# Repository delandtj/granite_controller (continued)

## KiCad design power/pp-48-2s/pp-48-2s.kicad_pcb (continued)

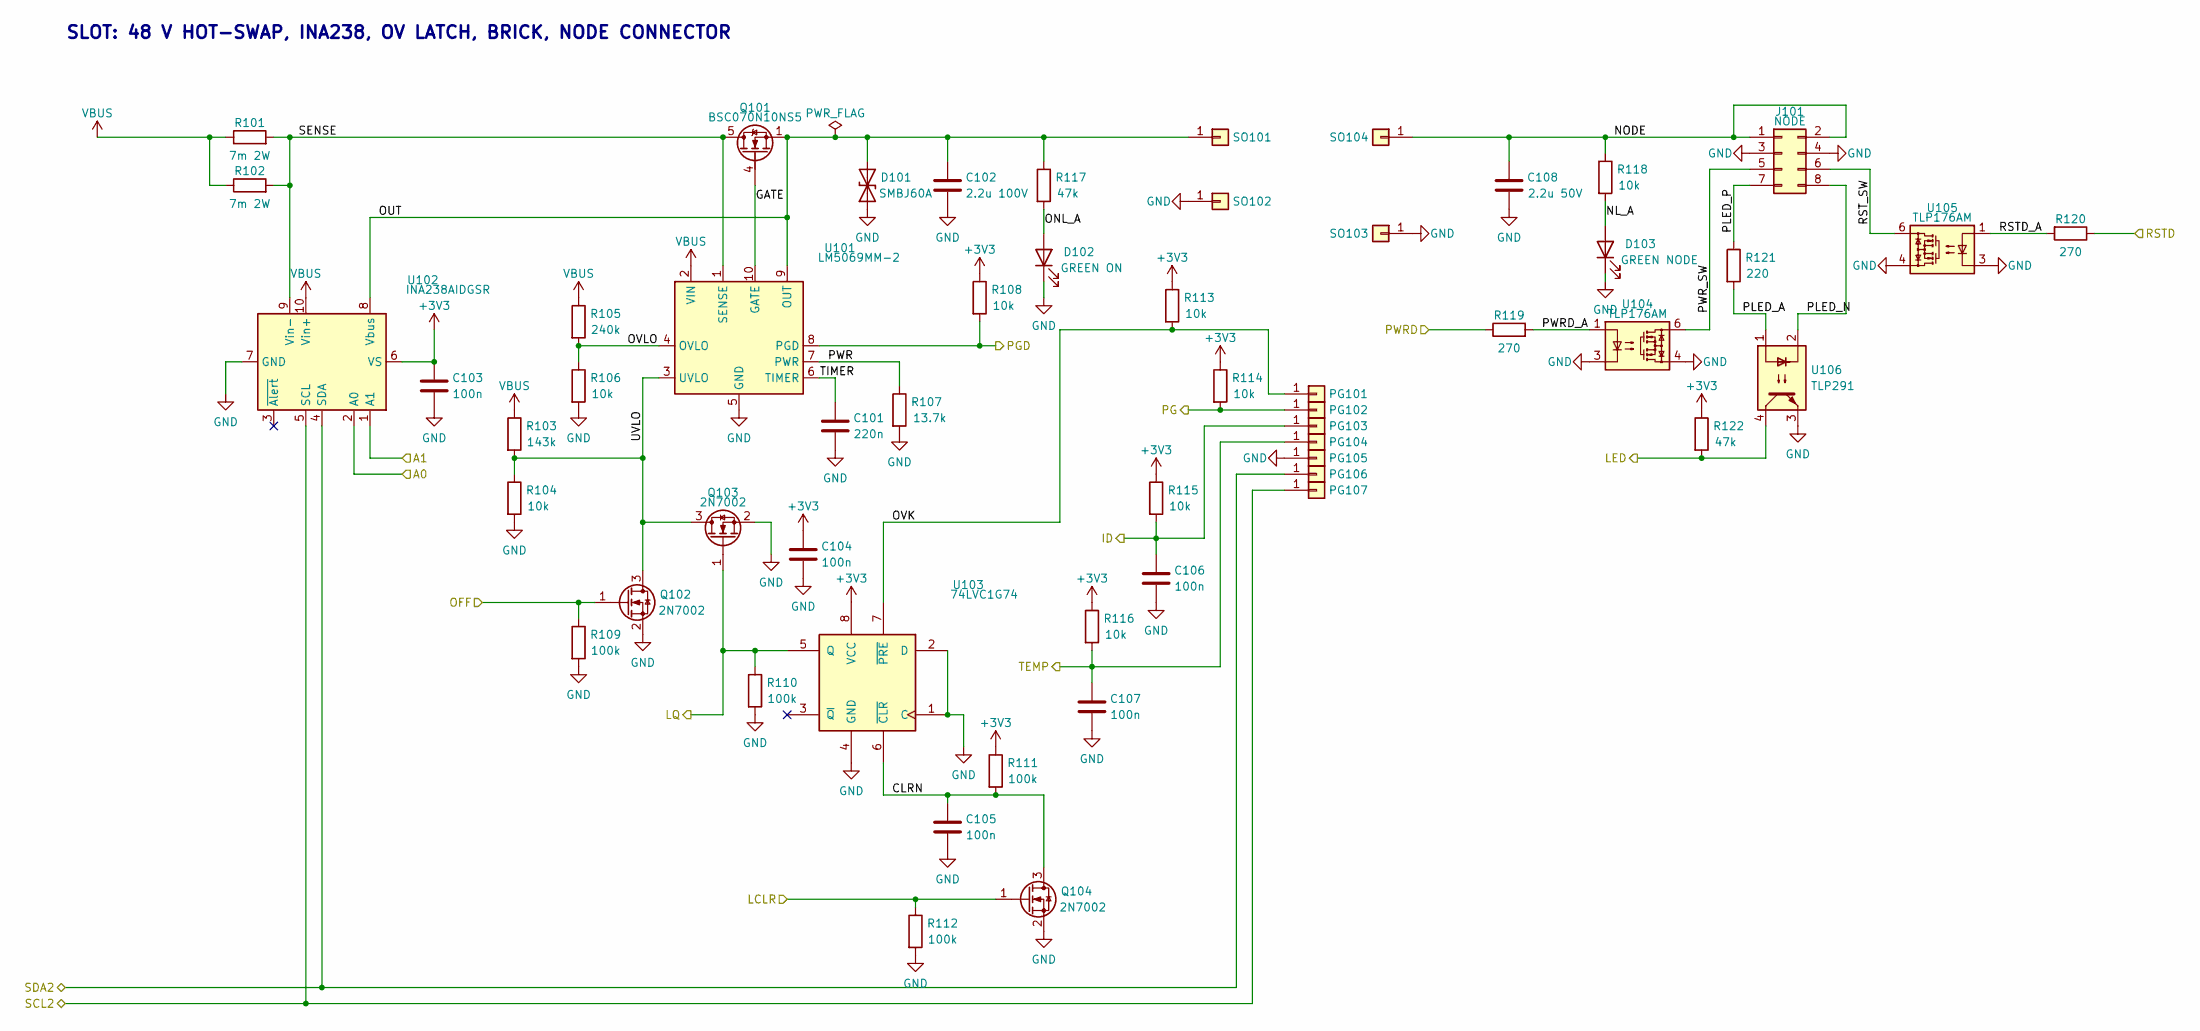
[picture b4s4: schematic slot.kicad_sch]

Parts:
C101: 220n; C_0603_1608Metric
C102: 2.2u 100V; C_1210_3225Metric; LCSC C338133
C103, C104, C105, C106, C107: 100n; C_0402_1005Metric; LCSC C1525
C108: 2.2u 50V; C_1210_3225Metric
D101: SMBJ60A; D_SMB; LCSC C353345
D102: GREEN ON; LED_0603_1608Metric; LCSC C2297
D103: GREEN NODE; LED_0603_1608Metric; LCSC C2297
J101: NODE; Molex_Mini-Fit_Jr_5566-08A_2x04_P4.20mm_Vertical; MPN Molex 39-28-1083
PG101, PG102, PG103, PG104, PG105, PG106, PG107: pogo; PM_Pogo_YZ130115073P; LCSC C5157258
Q101: BSC070N10NS5; TDSON-8-1
Q102, Q103, Q104: 2N7002; SOT-23; LCSC C8545
R101, R102: 7m 2W; R_2512_6332Metric; LCSC C2904232
R103: 143k; R_0805_2012Metric
R104, R106, R108, R113, R114, R115, R116: 10k; R_0402_1005Metric; LCSC C25744
R105: 240k; R_0805_2012Metric
R107: 13.7k; R_0402_1005Metric
R109, R110, R111, R112: 100k; R_0402_1005Metric; LCSC C25741
R117: 47k; R_1206_3216Metric
R118: 10k; R_0603_1608Metric; LCSC C25804
R119, R120: 270; R_0402_1005Metric; LCSC C22775
R121: 220; R_0402_1005Metric; LCSC C25091
R122: 47k; R_0402_1005Metric; LCSC C25792
SO101, SO102, SO103, SO104: M2x6 standoff; PM_Standoff_M2x6_SMTSO; LCSC C2915628
U101: LM5069MM-2; MSOP-10_3x3mm_P0.5mm; LCSC C111822
U102: INA238AIDGSR; TSSOP-10_3x3mm_P0.5mm
U103: 74LVC1G74; VSSOP-8_2.3x2mm_P0.5mm; LCSC C70285
U104, U105: TLP176AM; SOIC-4_4.55x3.7mm_P2.54mm; LCSC C5370540
U106: TLP291; SOIC-4_4.55x2.6mm_P1.27mm; LCSC C55144

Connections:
+3V3: C103.1, C104.1, R108.1, R111.1, R113.1, R114.1, R115.1, R116.1, R122.1, U102.6 (VS), U103.8 (VCC); also elsewhere on the board
/S1_ID: C106.1, PG103.1, R115.2; also elsewhere on the board
/S1_LCLR: Q104.1 (G), R112.1; also elsewhere on the board
/S1_LED: R122.2, U106.4; also elsewhere on the board
/S1_LQ: Q103.1 (G), R110.1, U103.5 (Q); also elsewhere on the board
/S1_OFF: Q102.1 (G), R109.1; also elsewhere on the board
/S1_PG: PG102.1, R114.2; also elsewhere on the board
/S1_PGD: R108.2, U101.8 (PGD); also elsewhere on the board
/S1_PWRD: R119.1; also elsewhere on the board
/S1_RSTD: R120.1; also elsewhere on the board
/S1_TEMP: C107.1, PG104.1, R116.2; also elsewhere on the board
/SCL2: PG107.1, U102.5 (SCL); also elsewhere on the board
/SDA2: PG106.1, U102.4 (SDA); also elsewhere on the board
/Slot 1/CLRN: C105.1, Q104.3 (D), R111.2, U103.6 (~CLR)
/Slot 1/GATE: Q101.4 (G), U101.10 (GATE)
/Slot 1/NL_A: D103.2 (A), R118.2
/Slot 1/NODE: C108.1, J101.1, J101.2, R118.1, SO104.1
/Slot 1/ONL_A: D102.2 (A), R117.2
/Slot 1/OUT: C102.1, D101.2 (A2), Q101.1 (S), Q101.2 (S), Q101.3 (S), R117.1, SO101.1, U101.9 (OUT), U102.8 (Vbus)
/Slot 1/OVK: PG101.1, R113.2, U103.7 (~PRE)
/Slot 1/OVLO: R105.2, R106.1, U101.4 (OVLO)
/Slot 1/PLED_A: R121.2, U106.1
/Slot 1/PLED_N: J101.8, U106.2
/Slot 1/PLED_P: J101.7, R121.1
/Slot 1/PWR: R107.1, U101.7 (PWR)
/Slot 1/PWRD_A: R119.2, U104.1
/Slot 1/PWR_SW: J101.5, U104.6
/Slot 1/RSTD_A: R120.2, U105.1
/Slot 1/RST_SW: J101.6, U105.6
/Slot 1/SENSE: Q101.5 (D), R101.2, R102.2, U101.1 (SENSE), U102.9 (Vin-)
/Slot 1/TIMER: C101.1, U101.6 (TIMER)
/Slot 1/UVLO: Q102.3 (D), Q103.3 (D), R103.2, R104.1, U101.3 (UVLO)
GND: C101.2, C102.2, C103.2, C104.2, C105.2, C106.2, C107.2, C108.2, D101.1 (A1), D102.1 (K), D103.1 (K), J101.3, J101.4, PG105.1, Q102.2 (S), Q103.2 (S), Q104.2 (S), R104.2, R106.2, R107.2, R109.2, R110.2, R112.2, SO102.1, SO103.1, U101.5 (GND), U102.1 (A1), U102.2 (A0), U102.7 (GND), U103.1 (C), U103.2 (D), U103.4 (GND), U104.3, U104.4, U105.3, U105.4, U106.3; also elsewhere on the board
VBUS: R101.1, R102.1, R103.1, R105.1, U101.2 (VIN), U102.10 (Vin+); also elsewhere on the board

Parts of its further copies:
C201: 220n; C_0603_1608Metric
C202: 2.2u 100V; C_1210_3225Metric; LCSC C338133
C203, C204, C205, C206, C207: 100n; C_0402_1005Metric; LCSC C1525
C208: 2.2u 50V; C_1210_3225Metric
D201: SMBJ60A; D_SMB; LCSC C353345
D202: GREEN ON; LED_0603_1608Metric; LCSC C2297
D203: GREEN NODE; LED_0603_1608Metric; LCSC C2297
J201: NODE; Molex_Mini-Fit_Jr_5566-08A_2x04_P4.20mm_Vertical; MPN Molex 39-28-1083
PG201, PG202, PG203, PG204, PG205, PG206, PG207: pogo; PM_Pogo_YZ130115073P; LCSC C5157258
Q201: BSC070N10NS5; TDSON-8-1
Q202, Q203, Q204: 2N7002; SOT-23; LCSC C8545
R201, R202: 7m 2W; R_2512_6332Metric; LCSC C2904232
R203: 143k; R_0805_2012Metric
R204, R206, R208, R213, R214, R215, R216: 10k; R_0402_1005Metric; LCSC C25744
R205: 240k; R_0805_2012Metric
R207: 13.7k; R_0402_1005Metric
R209, R210, R211, R212: 100k; R_0402_1005Metric; LCSC C25741
R217: 47k; R_1206_3216Metric
R218: 10k; R_0603_1608Metric; LCSC C25804
R219, R220: 270; R_0402_1005Metric; LCSC C22775
R221: 220; R_0402_1005Metric; LCSC C25091
R222: 47k; R_0402_1005Metric; LCSC C25792
SO201, SO202, SO203, SO204: M2x6 standoff; PM_Standoff_M2x6_SMTSO; LCSC C2915628
U201: LM5069MM-2; MSOP-10_3x3mm_P0.5mm; LCSC C111822
U202: INA238AIDGSR; TSSOP-10_3x3mm_P0.5mm
U203: 74LVC1G74; VSSOP-8_2.3x2mm_P0.5mm; LCSC C70285
U204, U205: TLP176AM; SOIC-4_4.55x3.7mm_P2.54mm; LCSC C5370540
U206: TLP291; SOIC-4_4.55x2.6mm_P1.27mm; LCSC C55144

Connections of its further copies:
+3V3: C203.1, C204.1, R208.1, R211.1, R213.1, R214.1, R215.1, R216.1, R222.1, U202.2 (A0), U202.6 (VS), U203.8 (VCC); also elsewhere on the board
/S2_ID: C206.1, PG203.1, R215.2; also elsewhere on the board
/S2_LCLR: Q204.1 (G), R212.1; also elsewhere on the board
/S2_LED: R222.2, U206.4; also elsewhere on the board
/S2_LQ: Q203.1 (G), R210.1, U203.5 (Q); also elsewhere on the board
/S2_OFF: Q202.1 (G), R209.1; also elsewhere on the board
/S2_PG: PG202.1, R214.2; also elsewhere on the board
/S2_PGD: R208.2, U201.8 (PGD); also elsewhere on the board
/S2_PWRD: R219.1; also elsewhere on the board
/S2_RSTD: R220.1; also elsewhere on the board
/S2_TEMP: C207.1, PG204.1, R216.2; also elsewhere on the board
/SCL2: PG207.1, U202.5 (SCL); also elsewhere on the board
/SDA2: PG206.1, U202.4 (SDA); also elsewhere on the board
/Slot 2/CLRN: C205.1, Q204.3 (D), R211.2, U203.6 (~CLR)
/Slot 2/GATE: Q201.4 (G), U201.10 (GATE)
/Slot 2/NL_A: D203.2 (A), R218.2
/Slot 2/NODE: C208.1, J201.1, J201.2, R218.1, SO204.1
/Slot 2/ONL_A: D202.2 (A), R217.2
/Slot 2/OUT: C202.1, D201.2 (A2), Q201.1 (S), Q201.2 (S), Q201.3 (S), R217.1, SO201.1, U201.9 (OUT), U202.8 (Vbus)
/Slot 2/OVK: PG201.1, R213.2, U203.7 (~PRE)
/Slot 2/OVLO: R205.2, R206.1, U201.4 (OVLO)
/Slot 2/PLED_A: R221.2, U206.1
/Slot 2/PLED_N: J201.8, U206.2
/Slot 2/PLED_P: J201.7, R221.1
/Slot 2/PWR: R207.1, U201.7 (PWR)
/Slot 2/PWRD_A: R219.2, U204.1
/Slot 2/PWR_SW: J201.5, U204.6
/Slot 2/RSTD_A: R220.2, U205.1
/Slot 2/RST_SW: J201.6, U205.6
/Slot 2/SENSE: Q201.5 (D), R201.2, R202.2, U201.1 (SENSE), U202.9 (Vin-)
/Slot 2/TIMER: C201.1, U201.6 (TIMER)
/Slot 2/UVLO: Q202.3 (D), Q203.3 (D), R203.2, R204.1, U201.3 (UVLO)
GND: C201.2, C202.2, C203.2, C204.2, C205.2, C206.2, C207.2, C208.2, D201.1 (A1), D202.1 (K), D203.1 (K), J201.3, J201.4, PG205.1, Q202.2 (S), Q203.2 (S), Q204.2 (S), R204.2, R206.2, R207.2, R209.2, R210.2, R212.2, SO202.1, SO203.1, U201.5 (GND), U202.1 (A1), U202.7 (GND), U203.1 (C), U203.2 (D), U203.4 (GND), U204.3, U204.4, U205.3, U205.4, U206.3; also elsewhere on the board
VBUS: R201.1, R202.1, R203.1, R205.1, U201.2 (VIN), U202.10 (Vin+); also elsewhere on the board

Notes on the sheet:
SLOT: 48 V HOT-SWAP, INA238, OV LATCH, BRICK, NODE CONNECTOR

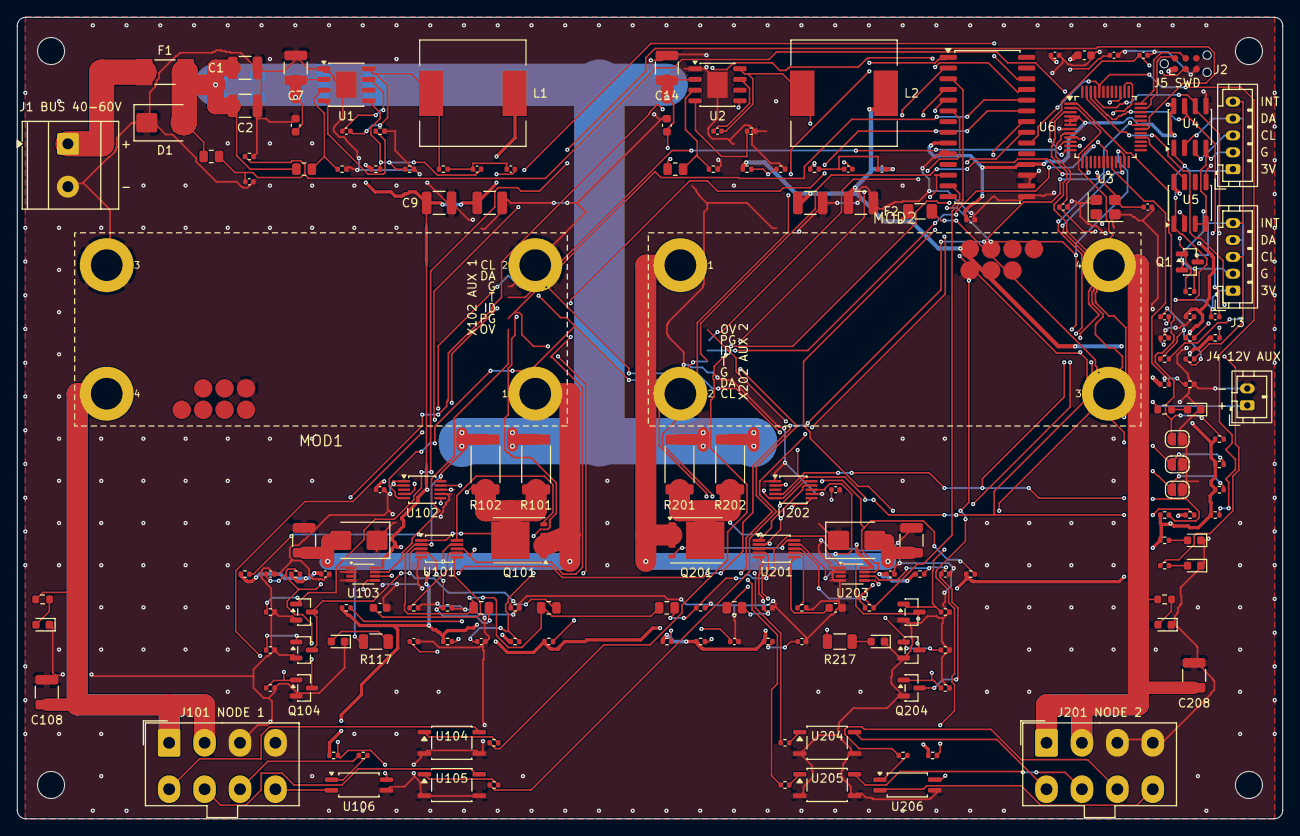
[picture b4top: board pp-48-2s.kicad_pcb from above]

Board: 4 copper layers, 150.0 x 95.0 mm, 198 parts (0 on the bottom side), 102 nets.

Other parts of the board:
C1, C2: 2.2u 100V; C_1210_3225Metric
C3: 10n; C_0402_1005Metric
C24, C25, C26, C27, C28: 100n; C_0402_1005Metric
D1: SMBJ60A; D_SMB
F1: 10A nano2; Fuse_Littelfuse-NANO2-451_453
H1, H2, H3, H4: MountingHole_3.2mm_M3
J1: BUS 40-60V; TerminalBlock_Phoenix_MKDS-3-2-5.08_1x02_P5.08mm_Horizontal
J2: CTRL IN; JST_PH_B5B-PH-K_1x05_P2.00mm_Vertical
J3: CTRL OUT; JST_PH_B5B-PH-K_1x05_P2.00mm_Vertical
MOD1, MOD2: PM_Module_Outline
Q1: 2N7002; SOT-23
R1: 470k; R_0805_2012Metric
R2: 13k; R_0402_1005Metric
R26, R27, R28, R29: 4.7k; R_0402_1005Metric
R30: 100k; R_0402_1005Metric
U4: ISO1640BD; SOIC-8_3.9x4.9mm_P1.27mm
U5: ISO7721D; SOIC-8_3.9x4.9mm_P1.27mm
U6: MCP23017-E/SO; SOIC-28W_7.5x17.9mm_P1.27mm

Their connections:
+3V3: C25.1, C27.1, C28.1, R26.1, R27.1, U4.8, U5.8, U6.9, U6.18; also elsewhere on the board
/EXP_IRQ: U6.20; also elsewhere on the board
/INT_OUT: U5.7; also elsewhere on the board
/Input/VBUS_IN: F1.1, J1.1
/Link/CTRL_INT: J2.5, J3.5, Q1.3
/Link/CTRL_SCL: J2.3, J3.3, R29.2, U4.3
/Link/CTRL_SDA: J2.4, J3.4, R28.2, U4.2
/Link/ISO_OUTA: Q1.1, R30.1, U5.2
/S1_LED: U6.26; also elsewhere on the board
/S1_LQ: U6.25; also elsewhere on the board
/S1_PG: U6.24; also elsewhere on the board
/S1_PGD: U6.23; also elsewhere on the board
/S1_PWRD: U6.21; also elsewhere on the board
/S1_RSTD: U6.22; also elsewhere on the board
/S2_LED: U6.6; also elsewhere on the board
/S2_LQ: U6.5; also elsewhere on the board
/S2_PG: U6.4; also elsewhere on the board
/S2_PGD: U6.3; also elsewhere on the board
/S2_PWRD: U6.1; also elsewhere on the board
/S2_RSTD: U6.2; also elsewhere on the board
/SCL1: R27.2, U4.6; also elsewhere on the board
/SCL2: U6.12; also elsewhere on the board
/SDA1: R26.2, U4.7; also elsewhere on the board
/SDA2: U6.13; also elsewhere on the board
/VBUS_SNS: C3.1, R1.2, R2.1; also elsewhere on the board
CTRL_3V3: C24.1, C26.1, J2.1, J3.1, R28.1, R29.1, U4.1, U5.1
CTRL_GND: C24.2, C26.2, J2.2, J3.2, Q1.2, R30.2, U4.4, U5.3, U5.4
GND: C1.2, C2.2, C3.2, C25.2, C27.2, C28.2, D1.1, J1.2, R2.2, U4.5, U5.5, U6.10, U6.15, U6.16, U6.17; also elsewhere on the board
VBUS: C1.1, C2.1, D1.2, F1.2, R1.1; also elsewhere on the board

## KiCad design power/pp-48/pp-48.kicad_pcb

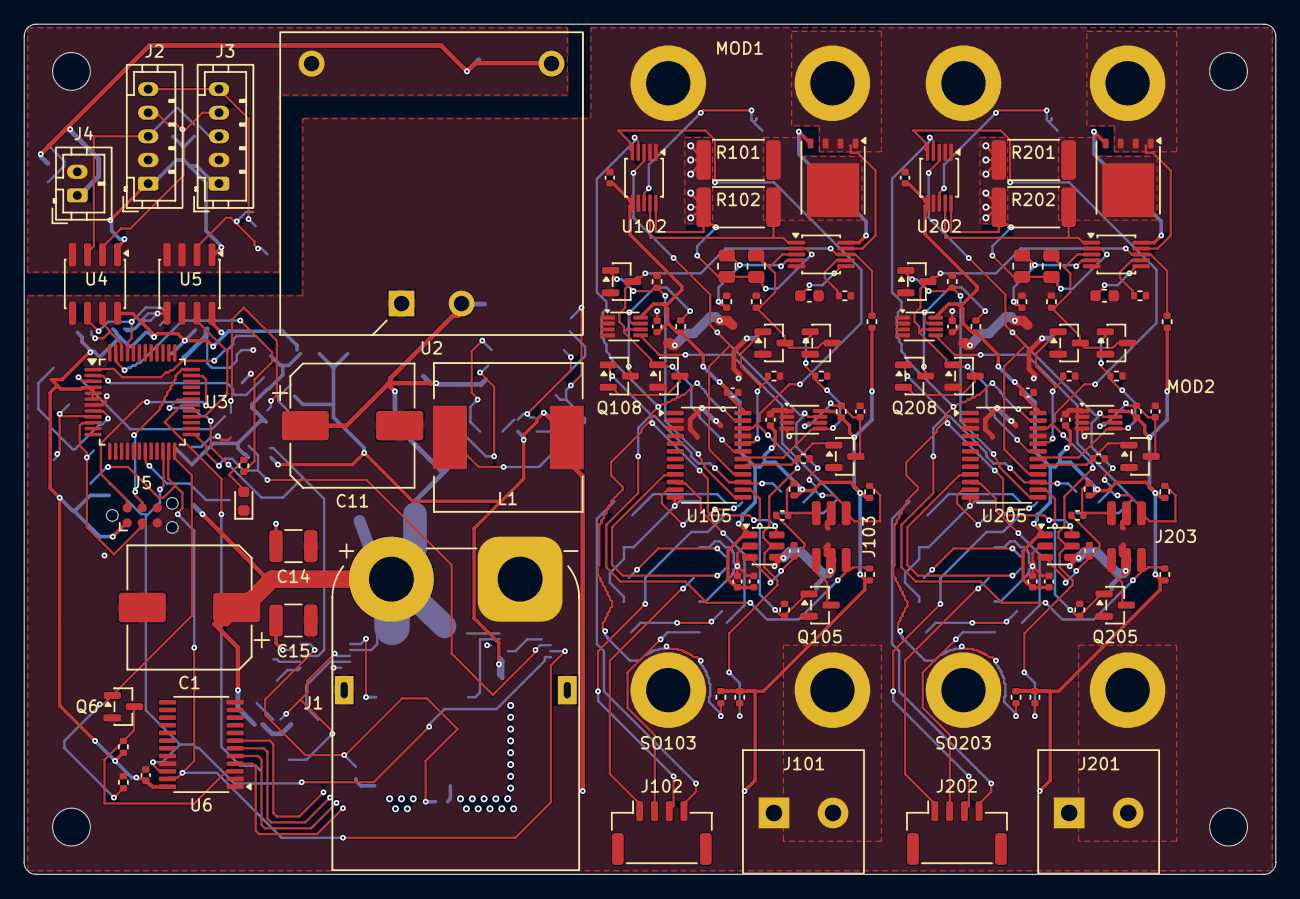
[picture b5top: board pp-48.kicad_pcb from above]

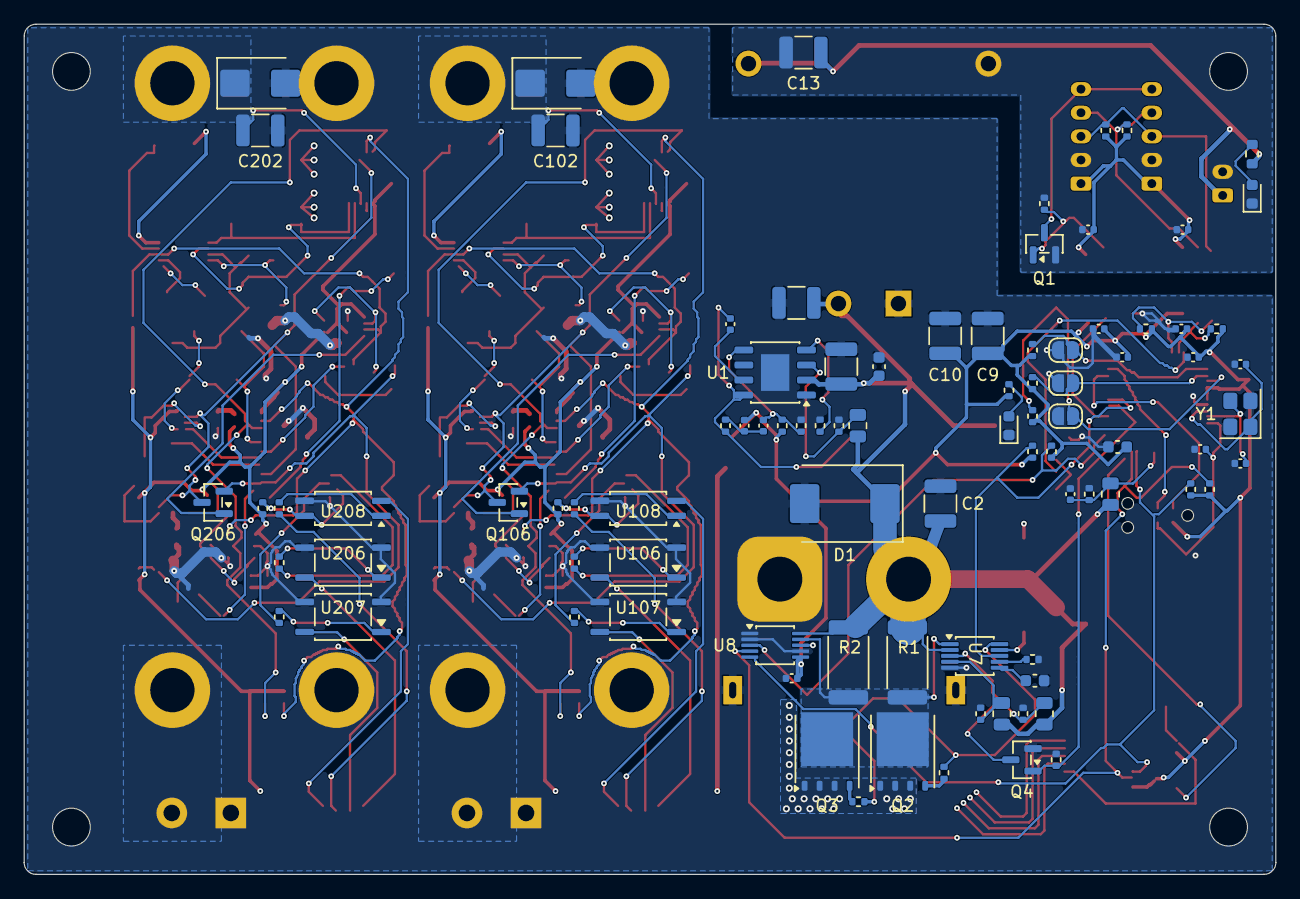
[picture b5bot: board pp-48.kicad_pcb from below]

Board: 4 copper layers, 106.0 x 72.0 mm, 218 parts (89 on the bottom side), 118 nets.

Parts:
C1: 47u 100V; CP_Elec_10x10
C2, C7, C12, C14, C15, C102, C202: 2.2u 100V; C_1210_3225Metric
C3, C101, C201: 220n; C_0603_1608Metric
C4: 2.2n 50V; C_0402_1005Metric
C5: 1.5n; C_0402_1005Metric
C6, C16, C17, C18, C20, C21, C24, C25, C26, C27, C28, C103, C104, C105, C106, C109, C110, C112, C203, C204, C205, C206, C209, C210, C212: 100n; C_0402_1005Metric
C8: 100n 100V; C_0603_1608Metric
C9, C10: 22u 10V; C_1210_3225Metric
C11: 22u 100V; CP_Elec_10x10
C13: 10u 50V; C_1210_3225Metric
C19: 4.7u; C_0603_1608Metric
C22, C23: 33p; C_0402_1005Metric
C111, C211: 1u; C_0402_1005Metric
D1: SMDJ60A; D_SMC
D3: GREEN 3V3; LED_0603_1608Metric
D4: GREEN RUN; LED_0603_1608Metric
D5: GREEN 12V; LED_0603_1608Metric
D101, D201: SMBJ60A; D_SMB
H1, H2, H3, H4: MountingHole_3.2mm_M3
J1: XT90PW-M; AMASS_XT90PW-M_1x02_P10.90mm_Horizontal
J2: CTRL IN; JST_PH_B5B-PH-K_1x05_P2.00mm_Vertical
J3: CTRL OUT; JST_PH_B5B-PH-K_1x05_P2.00mm_Vertical
J4: 12V AUX OUT; JST_PH_B2B-PH-K_1x02_P2.00mm_Vertical
J5: SWD; Tag-Connect_TC2030-IDC-NL_2x03_P1.27mm_Vertical
J101, J201: NODE 19V; TerminalBlock_Degson_DG128-5.0-02P
J102, J202: FRONT PANEL; JST_GH_SM04B-GHS-TB_1x04-1MP_P1.25mm_Horizontal
J103, J203: AUX; PM_Aux_Socket_2x03_P1.27
JP1: ADR0; SolderJumper-2_P1.3mm_Open_RoundedPad1.0x1.5mm
JP2: ADR1; SolderJumper-2_P1.3mm_Open_RoundedPad1.0x1.5mm
JP3: ADR2; SolderJumper-2_P1.3mm_Open_RoundedPad1.0x1.5mm
L1: 33u; L_12x12mm_H6mm
MOD1, MOD2: PM_Module_Outline
Q1, Q4, Q6, Q102, Q103, Q104, Q105, Q106, Q107, Q108, Q109, Q202, Q203, Q204, Q205, Q206, Q207, Q208, Q209: 2N7002; SOT-23
Q2, Q3: BSC040N10NS5; TDSON-8-1
Q101, Q201: BSC070N10NS5; TDSON-8-1
R1, R2: 4m 2W; R_2512_6332Metric
R3: 1M; R_0805_2012Metric
R4: 52.3k; R_0402_1005Metric
R5: 41.2k; R_0402_1005Metric
R6: 86.6k; R_0402_1005Metric
R7: 49.9k; R_0402_1005Metric
R8: 453k; R_0402_1005Metric
R9: 4.7k; R_0603_1608Metric
R10, R11: 10; R_0402_1005Metric
R12, R16, R31, R34, R38, R104, R108, R113, R114, R115, R204, R208, R213, R214, R215: 10k; R_0402_1005Metric
R14, R20, R21, R22, R30, R32, R109, R110, R111, R112, R123, R128, R129, R209, R210, R211, R212, R223, R228, R229: 100k; R_0402_1005Metric
R15: 220k; R_0805_2012Metric
R18, R19, R124, R224: 1k; R_0402_1005Metric
R23, R24: 2.2k; R_0402_1005Metric
R26, R27, R28, R29, R126, R127, R226, R227: 4.7k; R_0402_1005Metric
R33, R103, R203: 143k; R_0805_2012Metric
R35, R105, R205: 124k; R_0805_2012Metric
R36, R106, R206: 4.99k; R_0402_1005Metric
R37: 10.2k; R_0402_1005Metric
R101, R102, R201, R202: 7m 2W; R_2512_6332Metric
R107, R207: 13.7k; R_0402_1005Metric
R119, R120, R219, R220: 270; R_0402_1005Metric
R121, R221: 220; R_0402_1005Metric
R122, R222: 47k; R_0402_1005Metric
SO101, SO201: S1 VIN; PM_Standoff_M2x7_SMTSO
SO102, SO202: S2 GND; PM_Standoff_M2x7_SMTSO
SO103, SO203: S3 GND; PM_Standoff_M2x7_SMTSO
SO104, SO204: S4 VOUT; PM_Standoff_M2x7_SMTSO
U1: LM5164DDA; HSOP-8-1EP_3.9x4.9mm_P1.27mm_EP2.41x3.1mm
U2: URB4812YMD-6WR3; Converter_DCDC_1x1in_THT
U3: STM32G070CBT6; LQFP-48_7x7mm_P0.5mm
U4: ISO1640BD; SOIC-8_3.9x4.9mm_P1.27mm
U5: ISO7721D; SOIC-8_3.9x4.9mm_P1.27mm
U6: TCA9548APWR; TSSOP-24_4.4x7.8mm_P0.65mm
U7: LM5069MM-1; MSOP-10_3x3mm_P0.5mm
U8, U102, U202: INA238AIDGSR; TSSOP-10_3x3mm_P0.5mm
U101, U201: LM5069MM-2; MSOP-10_3x3mm_P0.5mm
U103, U110, U203, U210: 74LVC1G74; VSSOP-8_2.3x2mm_P0.5mm
U104, U204: ADC121C027CIMK; TSOT-23-6
U105, U205: TCA9535PWR; TSSOP-24_4.4x7.8mm_P0.65mm
U106, U107, U206, U207: TLP176AM; SOIC-4_4.55x3.7mm_P2.54mm
U108, U208: TLP291; SOIC-4_4.55x2.6mm_P1.27mm
Y1: 8MHz; Crystal_SMD_3225-4Pin_3.2x2.5mm

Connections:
+3V3: C5.2, C9.1, C10.1, C16.1, C18.1, C19.1, C20.1, C25.1, C27.1, C28.1, C103.1, C104.1, C109.1, C110.1, C111.1, C112.1, C203.1, C204.1, C209.1, C210.1, C211.1, C212.1, J5.1, L1.2, R6.1, R12.1, R18.1, R20.1, R21.1, R22.1, R23.1, R24.1, R26.1, R27.1, R31.1, R38.1, R108.1, R111.1, R113.1, R114.1, R115.1, R122.1, R126.1, R127.1, R128.1, R208.1, R211.1, R213.1, R214.1, R215.1, R222.1, R226.1, R227.1, R228.1, U3.4, U3.5, U3.6, U4.8, U5.8, U6.24, U8.6, U102.6, U103.8, U104.1, U105.24, U110.8, U202.6, U203.8, U204.1, U205.24, U210.8
/COL1_SCL: R127.2, U6.5, U102.5, U104.5, U105.22
/COL1_SDA: R126.2, U6.4, U102.4, U104.6, U105.23
/COL2_SCL: R227.2, U6.7, U202.5, U204.5, U205.22
/COL2_SDA: R226.2, U6.6, U202.4, U204.6, U205.23
/Column 1/ARM: Q106.1, U110.5
/Column 1/ARMS_M: Q108.2, Q109.3
/Column 1/ARMS_N: Q108.3, R128.2, U110.7
/Column 1/CLRN: C105.1, Q104.3, R111.2, U103.6
/Column 1/DISARM: Q107.1, R129.1, U105.13
/Column 1/GATE: Q101.4, U101.10
/Column 1/ID: J103.3, R115.2, R124.2
/Column 1/ID_F: C106.1, R124.1, U104.3
/Column 1/LCLR: Q104.1, R112.1, U105.17
/Column 1/LED: R122.2, U105.11, U108.4
/Column 1/LQ: Q103.1, R110.1, U103.5, U105.18
/Column 1/NODE: J101.2, SO104.1
/Column 1/OFF: Q102.1, R109.1, U105.20
/Column 1/OUT: C102.1, D101.1, Q101.1, Q101.2, Q101.3, SO101.1, U101.9, U102.8
/Column 1/OVK: J103.1, Q106.3, R113.2, U102.3, U103.7, U105.16
/Column 1/OVLO: R105.2, R106.1, U101.4
/Column 1/PG: J103.2, Q106.2, Q108.1, R114.2, U105.15
/Column 1/PGD: Q107.3, Q109.1, R108.2, U101.8, U105.19, U110.6
/Column 1/PLED_A: R121.2, U108.1
/Column 1/PLED_N: J102.4, U108.2
/Column 1/PLED_P: J102.3, R121.1
/Column 1/PWR: R107.1, U101.7
/Column 1/PWRD: R119.1, U105.9
/Column 1/PWRD_A: R119.2, U106.1
/Column 1/PWR_SW: J102.1, U106.6
/Column 1/RSTD: R120.1, U105.10
/Column 1/RSTD_A: R120.2, U107.1
/Column 1/RST_SW: J102.2, U107.6
/Column 1/RUN: J103.4, Q105.3
/Column 1/RUNOFF: Q105.1, R123.1, U105.14
/Column 1/SENSE: Q101.5, R101.2, R102.2, U101.1, U102.9
/Column 1/TIMER: C101.1, U101.6
/Column 1/UVLO: Q102.3, Q103.3, R103.2, R104.1, U101.3
/Column 2/ARM: Q206.1, U210.5
/Column 2/ARMS_M: Q208.2, Q209.3
/Column 2/ARMS_N: Q208.3, R228.2, U210.7
/Column 2/CLRN: C205.1, Q204.3, R211.2, U203.6
/Column 2/DISARM: Q207.1, R229.1, U205.13
/Column 2/GATE: Q201.4, U201.10
/Column 2/ID: J203.3, R215.2, R224.2
/Column 2/ID_F: C206.1, R224.1, U204.3
/Column 2/LCLR: Q204.1, R212.1, U205.17
/Column 2/LED: R222.2, U205.11, U208.4
/Column 2/LQ: Q203.1, R210.1, U203.5, U205.18
/Column 2/NODE: J201.2, SO204.1
/Column 2/OFF: Q202.1, R209.1, U205.20
/Column 2/OUT: C202.1, D201.1, Q201.1, Q201.2, Q201.3, SO201.1, U201.9, U202.8
/Column 2/OVK: J203.1, Q206.3, R213.2, U202.3, U203.7, U205.16
/Column 2/OVLO: R205.2, R206.1, U201.4
/Column 2/PG: J203.2, Q206.2, Q208.1, R214.2, U205.15
/Column 2/PGD: Q207.3, Q209.1, R208.2, U201.8, U205.19, U210.6
/Column 2/PLED_A: R221.2, U208.1
/Column 2/PLED_N: J202.4, U208.2
/Column 2/PLED_P: J202.3, R221.1
/Column 2/PWR: R207.1, U201.7
/Column 2/PWRD: R219.1, U205.9
/Column 2/PWRD_A: R219.2, U206.1
/Column 2/PWR_SW: J202.1, U206.6
/Column 2/RSTD: R220.1, U205.10
/Column 2/RSTD_A: R220.2, U207.1
/Column 2/RST_SW: J202.2, U207.6
/Column 2/RUN: J203.4, Q205.3
/Column 2/RUNOFF: Q205.1, R223.1, U205.14
/Column 2/SENSE: Q201.5, R201.2, R202.2, U201.1, U202.9
/Column 2/TIMER: C201.1, U201.6
/Column 2/UVLO: Q202.3, Q203.3, R203.2, R204.1, U201.3
/INT_OUT: U3.28, U5.7
/Input/GATE: R10.1, R11.2, U7.10
/Input/OVLO: R35.2, R36.1, U7.4
/Input/PWR: R37.1, U7.7
/Input/TIMER: C3.1, U7.6
/Input/TSENSE: Q2.5, Q3.5, R1.2, R2.2, U7.1, U8.9
/Input/UVLO: Q4.3, R33.2, R34.1, U7.3
/Link/CTRL_INT: J2.5, J3.5, Q1.3
/Link/CTRL_SCL: J2.3, J3.3, R29.2, U4.3
/Link/CTRL_SDA: J2.4, J3.4, R28.2, U4.2
/Link/ISO_OUTA: Q1.1, R30.1, U5.2
/MCU/ADR0: JP1.1, R20.2, U3.1
/MCU/ADR1: JP2.1, R21.2, U3.2
/MCU/ADR2: JP3.1, R22.2, U3.3
/MCU/LEDRUN_A: D4.2, R19.2
/MCU/LED_RUN: R19.1, U3.47
/MCU/NRST: C21.1, J5.3, U3.10
/MCU/OSC_IN: C22.1, U3.8, Y1.1
/MCU/OSC_OUT: C23.1, U3.9, Y1.3
/MCU/SWCLK: J5.4, U3.36
/MCU/SWDIO: J5.2, U3.35
/MUX_RST: Q6.1, R32.1, U3.24
/Mux/MUX_RSTN: Q6.3, R31.2, U6.3
/SCL1: R27.2, U3.45, U4.6
/SCL2: R24.2, U3.22, U6.22, U8.5
/SDA1: R26.2, U3.46, U4.7
/SDA2: R23.2, U3.23, U6.23, U8.4
/Supplies/BST1: C4.1, U1.7
/Supplies/EN1: R3.2, R4.1, U1.3
/Supplies/FB1: C6.2, R6.2, R7.1, U1.5
/Supplies/INJ1: C5.1, C6.1, R8.2
/Supplies/LED12_A: D5.2, R9.2
/Supplies/LED33_A: D3.2, R18.2
/Supplies/RON1: R5.1, U1.4
/Supplies/SW1: C4.2, L1.1, R8.1, U1.8
/TILE_AL: R12.2, U3.25, U8.3
/TILE_OFF: Q4.1, R14.1, U3.30
/TILE_PGD: R38.2, U3.31, U7.8
/VIN_SNS: C17.1, R15.2, R16.1, U3.19
CTRL_3V3: C24.1, C26.1, J2.1, J3.1, R28.1, R29.1, U4.1, U5.1
CTRL_12V: C13.1, J4.1, R9.1, U2.3
CTRL_GND: C13.2, C24.2, C26.2, D5.1, J2.2, J3.2, J4.2, Q1.2, R30.2, U2.5, U4.4, U5.3, U5.4
GND: C1.2, C2.2, C3.2, C7.2, C8.2, C9.2, C10.2, C11.2, C12.2, C14.2, C15.2, C16.2, C17.2, C18.2, C19.2, C20.2, C21.2, C22.2, C23.2, C25.2, C27.2, C28.2, C101.2, C102.2, C103.2, C104.2, C105.2, C106.2, C109.2, C110.2, C111.2, C112.2, C201.2, C202.2, C203.2, C204.2, C205.2, C206.2, C209.2, C210.2, C211.2, C212.2, D1.2, D3.1, D4.1, D101.2, D201.2, J1.1, J1.MP, J5.5, J101.1, J103.5, J103.6, J201.1, J203.5, J203.6, JP1.2, JP2.2, JP3.2, Q4.2, Q6.2, Q102.2, Q103.2, Q104.2, Q105.2, Q107.2, Q109.2, Q202.2, Q203.2, Q204.2, Q205.2, Q207.2, Q209.2, R4.2, R5.2, R7.2, R14.2, R16.2, R32.2, R34.2, R36.2, R37.2, R104.2, R106.2, R107.2, R109.2, R110.2, R112.2, R123.2, R129.2, R204.2, R206.2, R207.2, R209.2, R210.2, R212.2, R223.2, R229.2, SO102.1, SO103.1, SO202.1, SO203.1, U1.1, U1.9, U2.1, U3.7, U4.5, U5.5, U6.1, U6.2, U6.12, U6.21, U7.5, U8.1, U8.2, U8.7, U101.5, U102.1, U102.2, U102.7, U103.1, U103.2, U103.4, U104.2, U104.4, U105.2, U105.3, U105.12, U105.21, U106.3, U106.4, U107.3, U107.4, U108.3, U110.1, U110.2, U110.4, U201.5, U202.1, U202.2, U202.7, U203.1, U203.2, U203.4, U204.2, U204.4, U205.2, U205.3, U205.12, U205.21, U206.3, U206.4, U207.3, U207.4, U208.3, U210.1, U210.2, U210.4, Y1.2, Y1.4
unnamed: Q2.4, R10.2
unnamed: Q3.4, R11.1
VBUS: C14.1, C15.1, Q2.1, Q2.2, Q2.3, Q3.1, Q3.2, Q3.3, R101.1, R102.1, R103.1, R105.1, R201.1, R202.1, R203.1, R205.1, U7.9, U8.8, U101.2, U102.10, U201.2, U202.10
VIN: C1.1, C2.1, C7.1, C8.1, C11.1, C12.1, D1.1, J1.2, R1.1, R2.1, R3.1, R15.1, R33.1, R35.1, U1.2, U2.2, U7.2, U8.10
